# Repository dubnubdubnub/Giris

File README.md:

# Giris

An open source 32 key/half (64 total) **analog TMR split ortholinear keyboard** & 6 key macropad/dev board (`hw/TMR2615F_osu_pad`). 
Layout is similar to Keeb.io Iris with an extra column. Uses TMR2615F, 4:8 TMUX1574RSVR mux, & AT32F405. Link is UART over type-c cable.

There are 3 unique modes of operation: 
- standalone
- half A --> half B --> computer
- computer A <-- half A <--> half B --> computer B
    - Giris doubles as a KVM, you can control which computer you're typing on with a programmable macro
    - Relevant power circuitry to prevent backfeeding (GROUNDS ARE STILL BONDED!!!)

Done by Human:
- `hw/` — KiCad schematics and layout. `TMR2615F_osu_pad` is the 6-key development board the
  firmware is brought up on; `giris` is the full-size split.
- `mech/` — plates and frames.

Done by LLM + Human:
- `fw/` — firmware, written from scratch in C on the Artery BSP with TinyUSB. 8 kHz USB HS polling,
  8 kHz inter-half link. Host tools and a WebHID configurator live in `fw/tools/`.

## Schematics and photos

PDFs:

- **osu pad dev board** (built and running, pictured above):
  [schematic](hw/TMR2615F_osu_pad/output/TMR2615F_osu_pad.pdf) ·
  [PCB layers](hw/TMR2615F_osu_pad/output/TMR2615F_osu_pad-layers.pdf)
- **Giris split** (in layout): [schematic](hw/giris/output/giris.pdf)
- **More photos and video** of built boards: [`docs/photos/`](docs/photos/)

The schematic PDFs draw the per-key sheet once and list each key's designators at the end;
regenerate them with `hw/tools/sch_pdf.py`.

## Setup

This repo uses git submodules for its shared footprint/3D-model library (`hw/library`) and `hw/marbastlib`. **The 3D bodies will not appear in KiCad's 3D viewer unless the submodules are checked out**; `.step` files live in `hw/library/packages3d/`.

Clone with submodules:

```bash
git clone --recurse-submodules https://github.com/dubnubdubnub/Giris.git
```

If you already cloned without `--recurse-submodules`, initialize them after the fact:

```bash
git submodule update --init --recursive
```

> Note: `hw/marbastlib` may print an error while recursing into a nested `.history` submodule. That is harmless — it is upstream and holds no 3D models the boards need.

## 3D models

Footprint 3D bodies resolve from three locations:

- `${KICAD10_3DMODEL_DIR}/…` — the standard models shipped with KiCad.
- `${KIPRJMOD}/../library/packages3d/…` — this repo's `hw/library` submodule (must be checked out; see Setup).

When adding new 3D models to a board, reference them with one of the path variables above rather than a bare relative path (e.g. `../../packages3d/…`), so they resolve regardless of where the repo is cloned.

## Licence

Giris uses two licences:

| What | Licence | File |
|---|---|---|
| Firmware, host tools, web configurator, docs | **Apache-2.0** | [`LICENSE`](LICENSE) |
| Hardware — schematics, PCB, magnet models (`hw/`) | **CERN-OHL-P v2** | [`hw/LICENSE`](hw/LICENSE) |

Both are permissive: use it, change it, build it, sell it, no obligation to
publish your changes. Apache-2.0 additionally carries an explicit patent grant.
CERN-OHL-P is the hardware equivalent — software licences are written about
copying source, not about manufacturing a board.

New source files should carry an SPDX header:

```c
/* SPDX-License-Identifier: Apache-2.0
 * Copyright 2026 Isaac Chiu
 */
```

### Third-party code

[`THIRD_PARTY.md`](THIRD_PARTY.md) is the full inventory; [`NOTICE`](NOTICE)
carries the attributions that must accompany a distributed **binary**.

The short version: TinyUSB (MIT) and the ArteryTek BSP are fetched at build time
by `fw/tools/fetch-deps.sh` and are not in this repository, though both are linked
into firmware binaries. Three Artery-derived files *are* committed — the startup
file, the linker script and `at32f402_405_conf.h` — and keep Artery's notice
rather than Giris'. Note that Artery ships two licence statements that disagree;
`THIRD_PARTY.md` explains which one to rely on.

### Why the firmware is not GPL

Giris is written from scratch. libhmk, minipad, DeskHop and the VIA app are
GPL-3.0; QMK, vial-qmk and Keychron's fork are GPL-2.0. All were read as
references and **no source file was ever pasted out of any of them**. That is a
deliberate, ongoing constraint, not an accident — copying so much as a descriptor
struct would make this firmware copyleft.

This matters most for the USB XUSB (Xbox controller) interface, where both
reference implementations — libhmk and Keychron's QMK fork — are copyleft. Write
it from Microsoft's own specification instead:

> **[MS-XUSBI]** — *Xbox Universal Serial Bus Protocol (XUSB) Interface Extension*
> <https://learn.microsoft.com/en-us/openspecs/windows_protocols/ms-xusbi/c79474e7-3968-43d1-8d2f-175d47bef43e>

It gives the class triple and the 20-byte report normatively, and its Open
Specifications notice explicitly permits copying the documentation in order to
build implementations of it. [`THIRD_PARTY.md`](THIRD_PARTY.md) records the
limits of that permission — notably that no patent grant is established.

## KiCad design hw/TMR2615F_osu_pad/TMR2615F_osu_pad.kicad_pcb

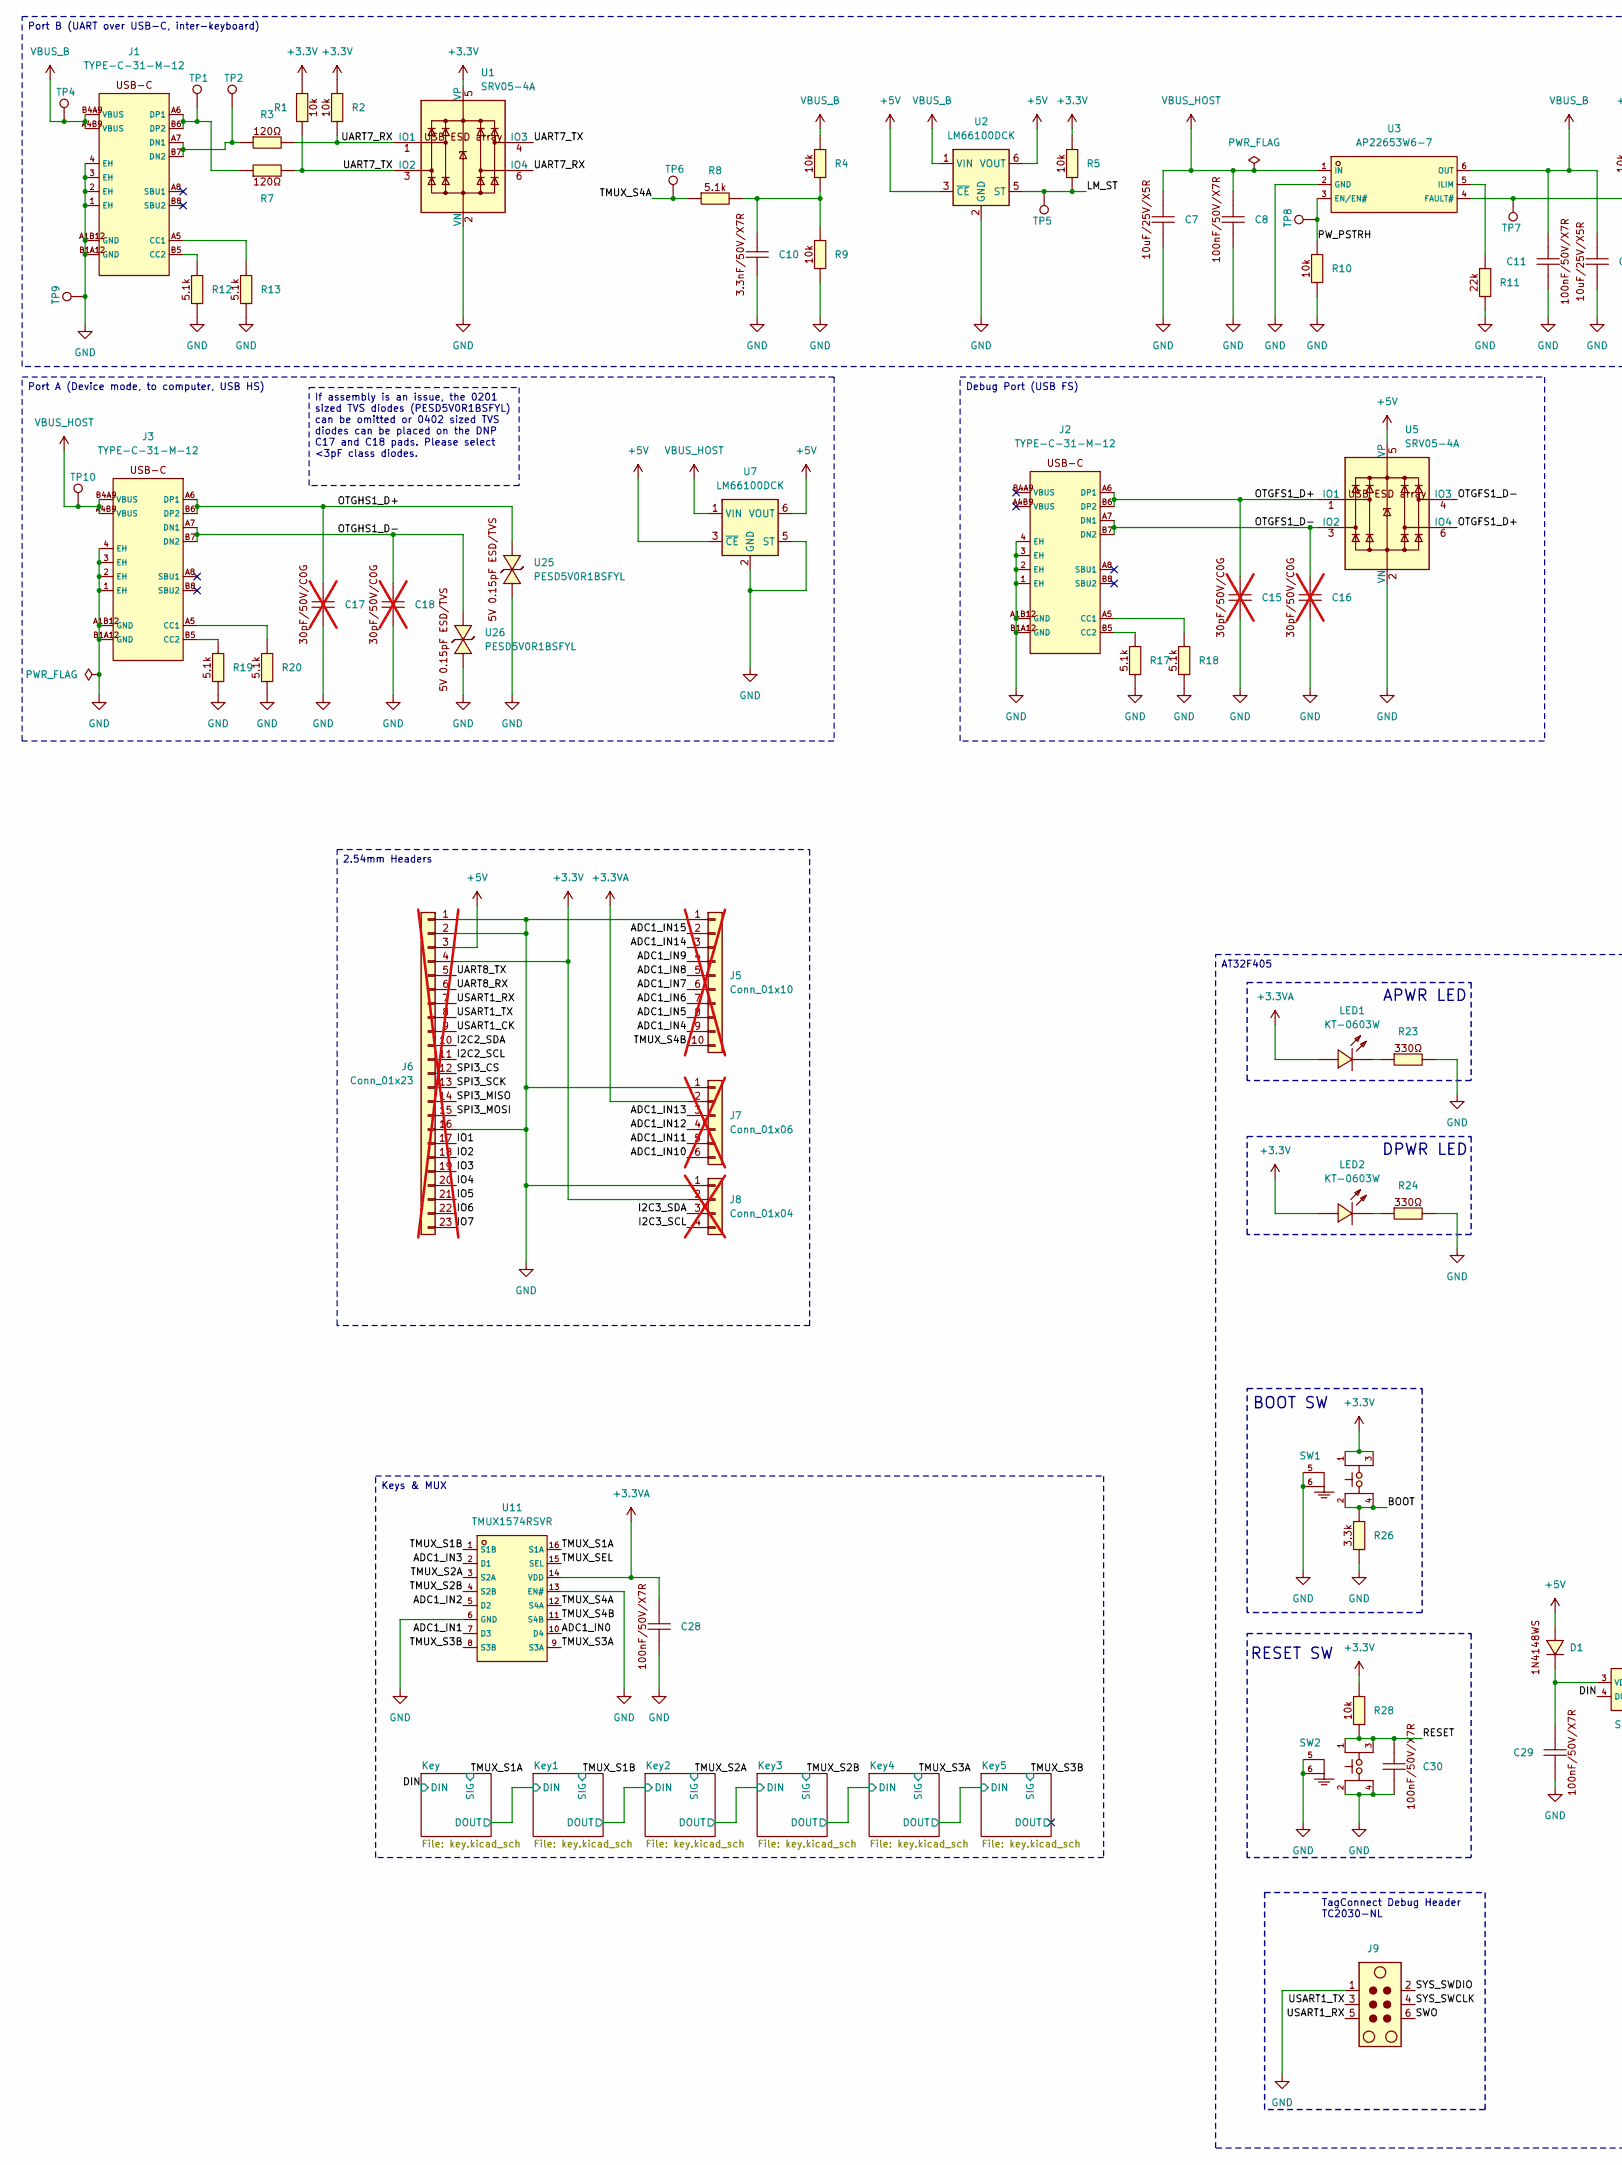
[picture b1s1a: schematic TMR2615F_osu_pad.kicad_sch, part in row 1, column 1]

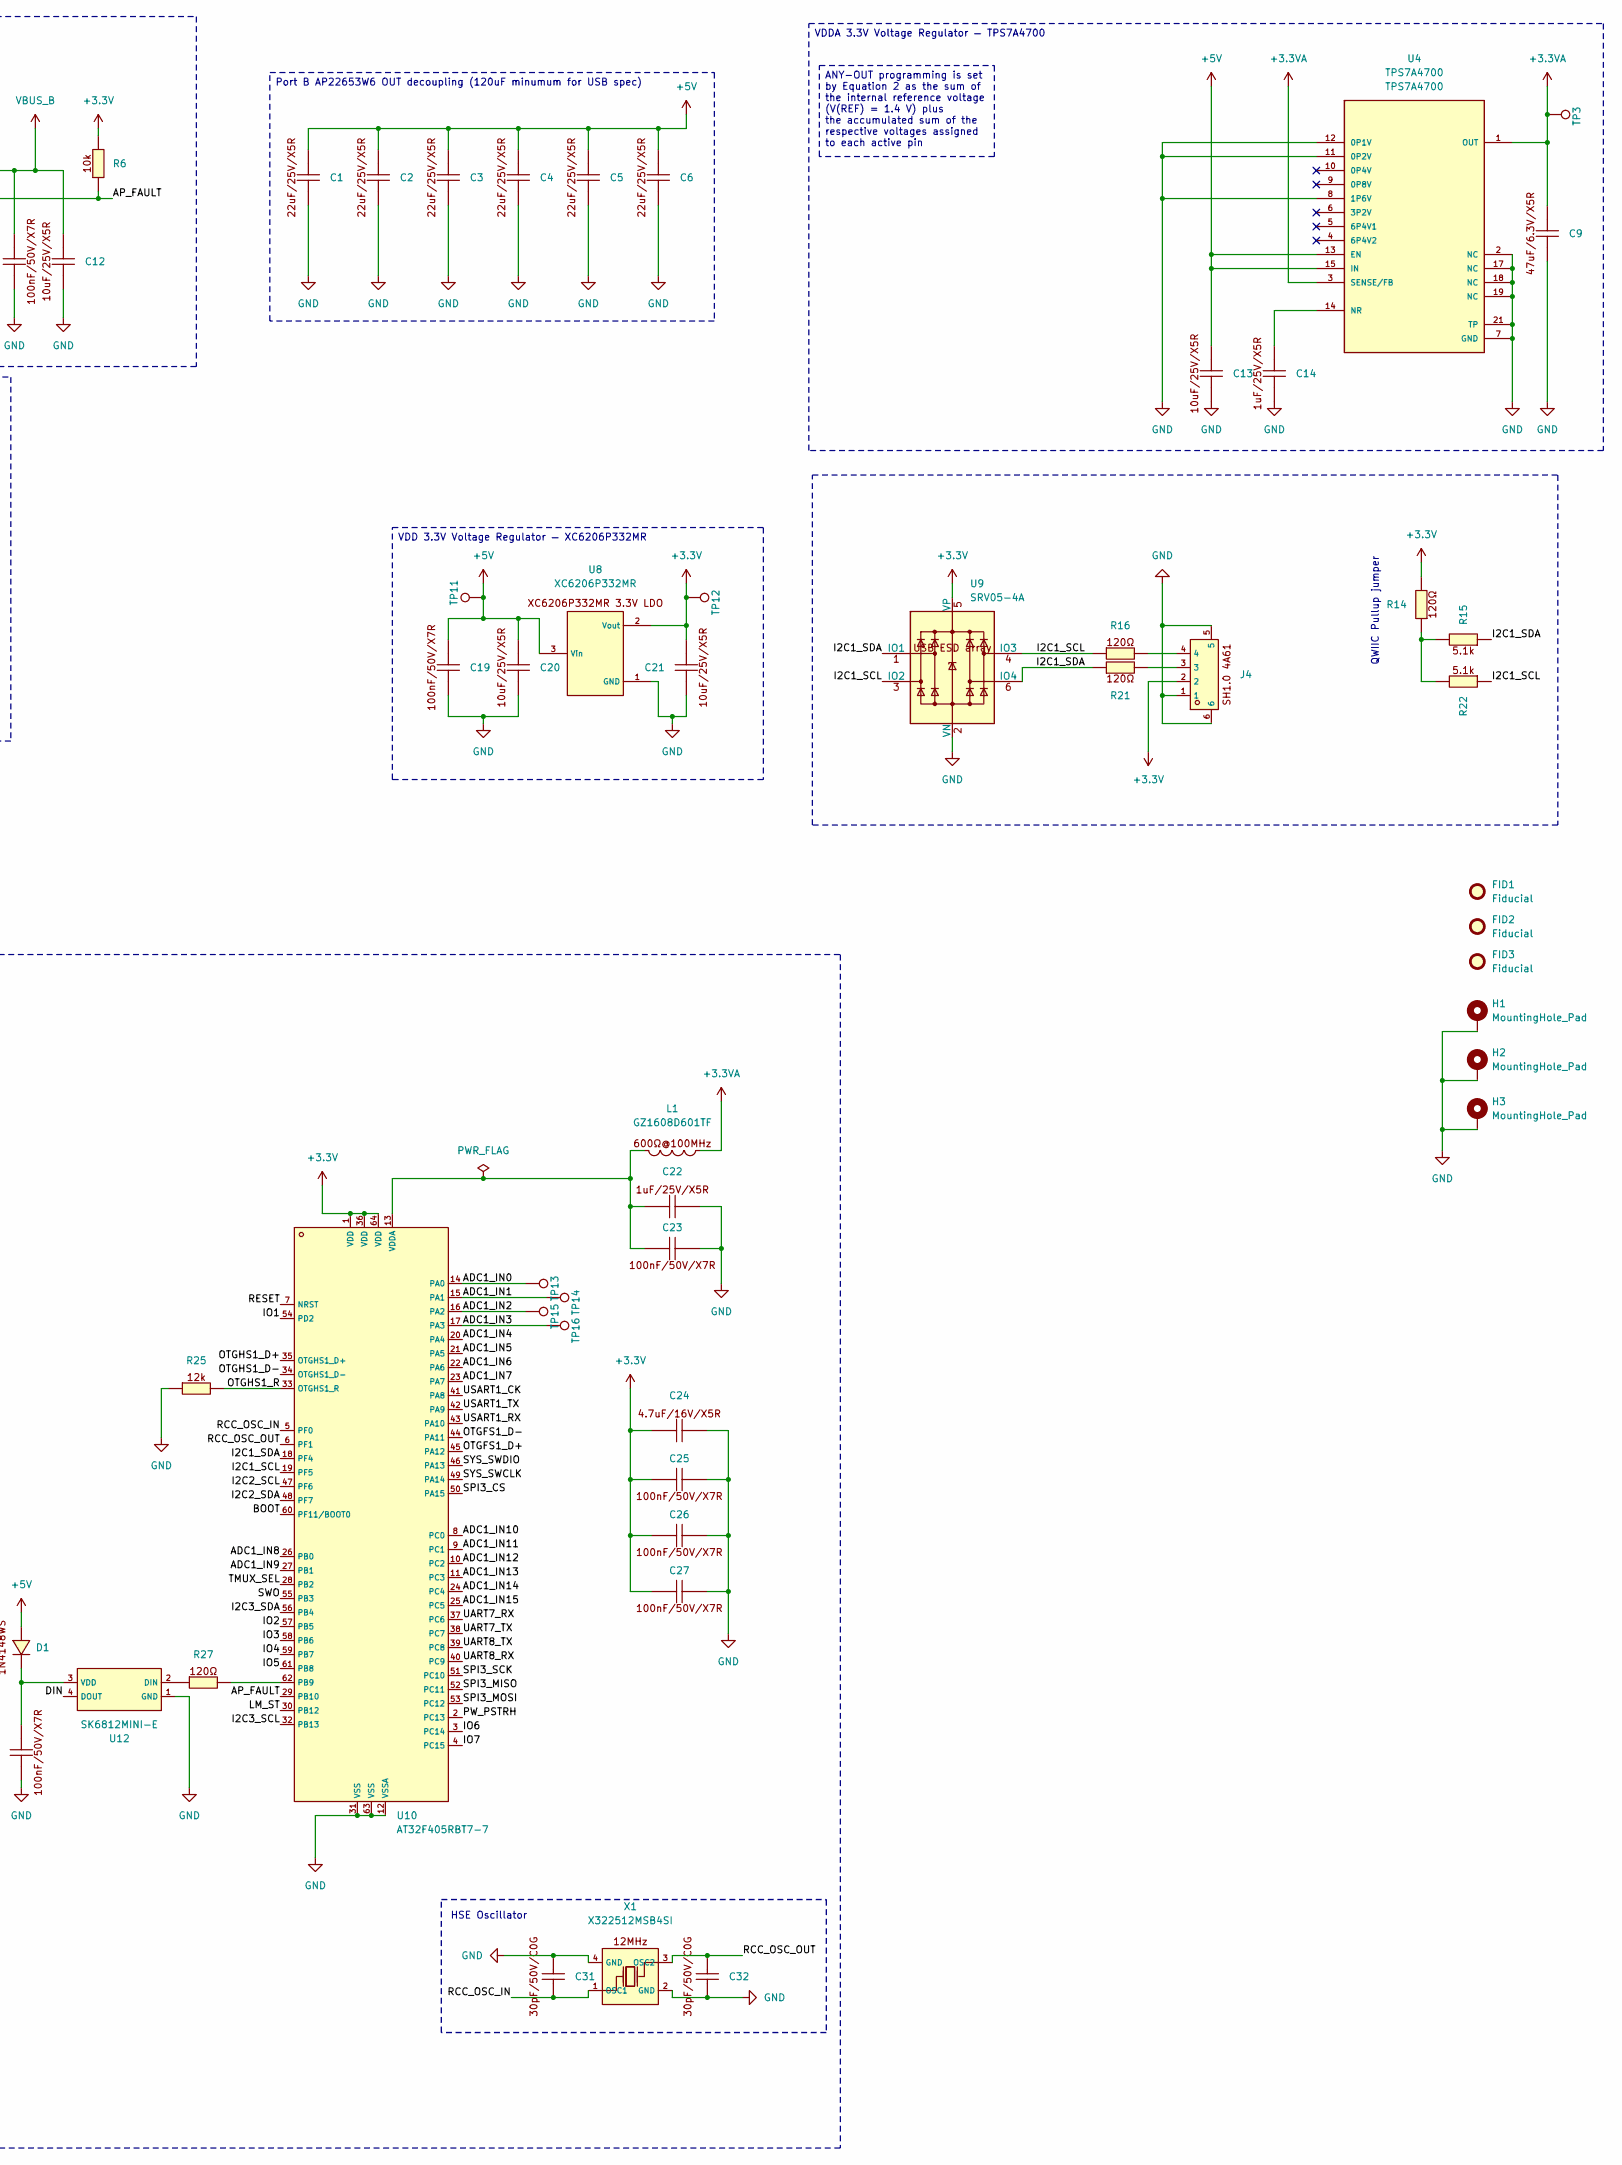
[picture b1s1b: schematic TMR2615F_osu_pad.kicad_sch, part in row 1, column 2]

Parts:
C1, C2, C3, C4, C5, C6: CL21A226MAQNNNE; C_0805_2012Metric; LCSC C45783
C7, C12, C13, C20, C21: CL21A106KAYNNNE; C_0805_2012Metric; LCSC C15850
C8, C11, C19, C23, C25, C26, C27, C28, C29, C30: CL05B104KB54PNC; C_0402_1005Metric; LCSC C307331
C9: CL21A476MQYNNNE; C_0805_2012Metric; LCSC C16780
C10: CL10B332KB8NNNC; C_0603_1608Metric; LCSC C1613
C14, C22: CL05A105KA5NQNC; C_0402_1005Metric; LCSC C52923
C15, C16, C17, C18: 0402CG300J500NT; C_0402_1005Metric; LCSC C1570; not fitted
C24: CL10A475KO8NNNC; C_0603_1608Metric; LCSC C19666
C31, C32: 0402CG300J500NT; C_0402_1005Metric; LCSC C1570
D1: 1N4148WS_T4; D_SOD-323_HandSoldering; LCSC C2128
FID1, FID2, FID3: Fiducial; Fiducial_1mm_Mask2mm
H1, H2, H3: MountingHole_Pad; MountingHole_2.2mm_M2_Pad_Via
J1, J2, J3: TYPE-C-31-M-12; USB-C_SMD-TYPE-C-31-M-12_1; LCSC C165948
J4: XY-SH1_0-4A61; CONN-SMD_4P-P1.00_XYECONN_XY-SH1.0-4A61; LCSC C19271998
J5: Conn_01x10; PinHeader_1x10_P2.54mm_Vertical; not fitted
J6: Conn_01x23; PinHeader_1x23_P2.54mm_Vertical; not fitted
J7: Conn_01x06; PinHeader_1x06_P2.54mm_Vertical; not fitted
J8: Conn_01x04; PinHeader_1x04_P2.54mm_Vertical; not fitted
J9: Tag-Connect_TC2030-IDC-NL_2x03_P1.27mm_Vertical
L1: GZ1608D601TF; L_0603_1608Metric; LCSC C1002
LED1, LED2: KT-0603W; LED0603-R-RD_WHITE; LCSC C2290
R1, R2, R4, R5, R6, R9, R10, R28: 0402WGF1002TCE; R_0402_1005Metric; LCSC C25744
R3, R7, R14, R16, R21, R27: 0402WGF1200TCE; R_0402_1005Metric; LCSC C25079
R8, R12, R13, R15, R17, R18, R19, R20, R22: 0402WGF5101TCE; R_0402_1005Metric; LCSC C25905
R11: 0402WGF2202TCE; R_0402_1005Metric; LCSC C25768
R23, R24: 0402WGF3300TCE; R_0402_1005Metric; LCSC C25104
R25: 0402WGF1202TCE; R_0402_1005Metric; LCSC C25752
R26: 0402WGF3301TCE; R_0402_1005Metric; LCSC C25890
SW1, SW2: SKSGPAE010; SW-SMD_SKSGAAE010; LCSC C125045
TP1, TP2, TP3, TP4, TP5, TP6, TP7, TP8, TP9, TP10, TP11, TP12, TP13, TP14, TP15, TP16: TestPoint; TestPoint_Pad_D1.0mm
U1, U5, U9: SRV05-4A; SOT-23-6; LCSC ID C20615829
U2, U7: LM66100DCK; SOT-363_SC-70-6; LCSC C2869734
U3: AP22653W6-7; SOT-23-6_L2.9-W1.6-P0.95-LS2.8-BR; LCSC C2158037
U4: TPS7A4700; VQFN-20_L5.0-W5.0-P0.65-TL-EP; LCSC C28286
U8: XC6206P332MR; SOT-23-3_L2.9-W1.6-P1.90-LS2.8-BR; LCSC C5446
U10: AT32F405RBT7-7; LQFP-64_L7.0-W7.0-P0.40-LS9.0-BL; LCSC C47115472
U11: TMUX1574RSVR; UQFN-16_L2.6-W1.8-P0.40-BL; LCSC C2673120
U12: SK6812MINI-E; LED-SMD_4P-L3.2-W2.8-LS5.9_SK6812MINI-E; LCSC C5149201
U25, U26: PESD5V0R1BSFYL; SOD-962_L0.6-W0.3-BI; LCSC C461221
X1: X322512MSB4SI; LCSC C9002

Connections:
+3.3V: C21.1, C24.1, C25.2, C26.2, C27.2, J4.2, J6.4, J8.2, LED2.1 (A), R1.2, R2.2, R5.2, R6.2, R14.2, R28.2, SW1.1, SW1.3, TP12.1 (1_1), U1.5 (VP), U8.2 (Vout), U9.5 (VP), U10.1 (VDD), U10.36 (VDD), U10.64 (VDD)
+3.3VA: C9.2, C28.2, J7.2, L1.2, LED1.1 (A), TP3.1 (1_1), U4.1 (OUT), U4.3 (SENSE/FB), U4.20 (OUT), U11.14 (VDD); also elsewhere on the board
+5V: C1.2, C2.2, C3.2, C4.2, C5.2, C6.2, C13.2, C19.2, C20.2, D1.2 (A), J6.3, TP11.1 (1_1), U2.3 (~CE), U2.6 (VOUT), U4.13 (EN), U4.15 (IN), U4.16 (IN), U5.5 (VP), U7.3 (~CE), U7.6 (VOUT), U8.3 (Vin); also elsewhere on the board
/ADC1_IN0: TP13.1 (1_1), U10.14 (PA0), U11.10 (D4)
/ADC1_IN1: TP14.1 (1_1), U10.15 (PA1), U11.7 (D3)
/ADC1_IN2: TP15.1 (1_1), U10.16 (PA2), U11.5 (D2)
/ADC1_IN3: TP16.1 (1_1), U10.17 (PA3), U11.2 (D1)
/ADC1_IN4: J5.9, U10.20 (PA4)
/ADC1_IN5: J5.8, U10.21 (PA5)
/ADC1_IN6: J5.7, U10.22 (PA6)
/ADC1_IN7: J5.6, U10.23 (PA7)
/ADC1_IN8: J5.5, U10.26 (PB0)
/ADC1_IN9: J5.4, U10.27 (PB1)
/ADC1_IN10: J7.6, U10.8 (PC0)
/ADC1_IN11: J7.5, U10.9 (PC1)
/ADC1_IN12: J7.4, U10.10 (PC2)
/ADC1_IN13: J7.3, U10.11 (PC3)
/ADC1_IN14: J5.3, U10.24 (PC4)
/ADC1_IN15: J5.2, U10.25 (PC5)
/AP_FAULT: R6.1, TP7.1 (1_1), U3.4 (FAULT#), U10.29 (PB10)
/BOOT: R26.2, SW1.2, SW1.4, U10.60 (PF11/BOOT0)
/DIN: U12.4 (DOUT); also elsewhere on the board
/I2C1_SCL: R16.1, R22.1, U9.3 (IO2), U9.4 (IO3), U10.19 (PF5)
/I2C1_SDA: R15.1, R21.1, U9.1 (IO1), U9.6 (IO4), U10.18 (PF4)
/I2C2_SCL: J6.11, U10.47 (PF6)
/I2C2_SDA: J6.10, U10.48 (PF7)
/I2C3_SCL: J8.4, U10.32 (PB13)
/I2C3_SDA: J8.3, U10.56 (PB4)
/IO1: J6.17, U10.54 (PD2)
/IO2: J6.18, U10.57 (PB5)
/IO3: J6.19, U10.58 (PB6)
/IO4: J6.20, U10.59 (PB7)
/IO5: J6.21, U10.61 (PB8)
/IO6: J6.22, U10.3 (PC14)
/IO7: J6.23, U10.4 (PC15)
/LM_ST: R5.1, TP5.1 (1_1), U2.5 (ST), U10.30 (PB12)
/OTGFS1_D+: C15.2, J2.A6 (DP1), J2.B6 (DP2), U5.1 (IO1), U5.6 (IO4), U10.45 (PA12)
/OTGFS1_D-: C16.2, J2.A7 (DN1), J2.B7 (DN2), U5.3 (IO2), U5.4 (IO3), U10.44 (PA11)
/OTGHS1_D+: C17.2, J3.A6 (DP1), J3.B6 (DP2), U10.35 (OTGHS1_D+), U25.2
/OTGHS1_D-: C18.2, J3.A7 (DN1), J3.B7 (DN2), U10.34 (OTGHS1_D-), U26.2
/OTGHS1_R: R25.2, U10.33 (OTGHS1_R)
/PW_PSTRH: R10.2, TP8.1 (1_1), U3.3 (EN/EN#), U10.2 (PC13)
/RCC_OSC_IN: C31.1, U10.5 (PF0), X1.1 (OSC1)
/RCC_OSC_OUT: C32.2, U10.6 (PF1), X1.3 (OSC2)
/RESET: C30.2, R28.1, SW2.1, SW2.3, U10.7 (NRST)
/SPI3_CS: J6.12, U10.50 (PA15)
/SPI3_MISO: J6.14, U10.52 (PC11)
/SPI3_MOSI: J6.15, U10.53 (PC12)
/SPI3_SCK: J6.13, U10.51 (PC10)
/SWO: J9.6, U10.55 (PB3)
/SYS_SWCLK: J9.4, U10.49 (PA14)
/SYS_SWDIO: J9.2, U10.46 (PA13)
/TMUX_S1A: U11.16 (S1A); also elsewhere on the board
/TMUX_S1B: U11.1 (S1B); also elsewhere on the board
/TMUX_S2A: U11.3 (S2A); also elsewhere on the board
/TMUX_S2B: U11.4 (S2B); also elsewhere on the board
/TMUX_S3A: U11.9 (S3A); also elsewhere on the board
/TMUX_S3B: U11.8 (S3B); also elsewhere on the board
/TMUX_S4A: R8.1, TP6.1 (1_1), U11.12 (S4A)
/TMUX_S4B: J5.10, U11.11 (S4B)
/TMUX_SEL: U10.28 (PB2), U11.15 (SEL)
/UART7_RX: R2.1, R3.2, U1.1 (IO1), U1.6 (IO4), U10.37 (PC6)
/UART7_TX: R1.1, R7.2, U1.3 (IO2), U1.4 (IO3), U10.38 (PC7)
/UART8_RX: J6.6, U10.40 (PC9)
/UART8_TX: J6.5, U10.39 (PC8)
/USART1_CK: J6.9, U10.41 (PA8)
/USART1_RX: J6.7, J9.5, U10.43 (PA10)
/USART1_TX: J6.8, J9.3, U10.42 (PA9)
GND: C1.1, C2.1, C3.1, C4.1, C5.1, C6.1, C7.2, C8.1, C9.1, C10.1, C11.1, C12.2, C13.1, C14.1, C15.1, C16.1, C17.1, C18.1, C19.1, C20.1, C21.2, C22.2, C23.1, C24.2, C25.1, C26.1, C27.1, C28.1, C29.1, C30.1, C31.2, C32.1, H1.1 (1_1), H2.1 (1_1), H3.1 (1_1), J1.1 (EH), J1.2 (EH), J1.3 (EH), J1.4 (EH), J1.A1B12 (GND), J1.B1A12 (GND), J2.1 (EH), J2.2 (EH), J2.3 (EH), J2.4 (EH), J2.A1B12 (GND), J2.B1A12 (GND), J3.1 (EH), J3.2 (EH), J3.3 (EH), J3.4 (EH), J3.A1B12 (GND), J3.B1A12 (GND), J4.1, J4.5, J4.6, J5.1, J6.1, J6.2, J6.16, J7.1, J8.1, J9.1, R9.1, R10.1, R11.1, R12.1, R13.1, R17.1, R18.1, R19.1, R20.1, R23.2, R24.2, R25.1, R26.1, SW1.5, SW1.6, SW2.2, SW2.4, SW2.5, SW2.6, TP9.1 (1_1), U1.2 (VN), U2.2 (GND), U3.2 (GND), U4.2 (NC), U4.7 (GND), U4.8 (1P6V), U4.11 (0P2V), U4.12 (0P1V), U4.17 (NC), U4.18 (NC), U4.19 (NC), U4.21 (TP), U5.2 (VN), U7.2 (GND), U7.5 (ST), U8.1 (GND), U9.2 (VN), U10.12 (VSSA), U10.31 (VSS), U10.63 (VSS), U11.6 (GND), U11.13 (EN#), U12.1 (GND), U25.1, U26.1, X1.2 (GND), X1.4 (GND); also elsewhere on the board
unnamed: C10.2, R4.1, R8.2, R9.2
unnamed: C29.2, D1.1 (K), U12.3 (VDD)
unnamed: J1.A5 (CC1), R13.2
unnamed: J1.B5 (CC2), R12.2
unnamed: J1.A7 (DN1), J1.B7 (DN2), R3.1, TP2.1 (1_1)
unnamed: J1.A6 (DP1), J1.B6 (DP2), R7.1, TP1.1 (1_1)
unnamed: J2.A5 (CC1), R18.2
unnamed: J2.B5 (CC2), R17.2
unnamed: J3.A5 (CC1), R20.2
unnamed: J3.B5 (CC2), R19.2
unnamed: J4.3, R21.2
unnamed: J4.4, R16.2
unnamed: LED1.2 (K), R23.1
unnamed: LED2.2 (K), R24.1
unnamed: R14.1, R15.2, R22.2
unnamed: R11.2, U3.5 (ILIM)
unnamed: C14.2, U4.14 (NR)
unnamed: R27.2, U10.62 (PB9)
unnamed: C22.1, C23.2, L1.1, U10.13 (VDDA)
unnamed: R27.1, U12.2 (DIN)
VBUS_B: C11.2, C12.1, J1.A4B9 (VBUS), J1.B4A9 (VBUS), R4.2, TP4.1 (1_1), U2.1 (VIN), U3.6 (OUT)
VBUS_HOST: C7.1, C8.2, J3.A4B9 (VBUS), J3.B4A9 (VBUS), TP10.1 (1_1), U3.1 (IN), U7.1 (VIN)

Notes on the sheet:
APWR LED
TagConnect Debug Header TC2030-NL
BOOT SW
QWIIC Pullup jumper
HSE Oscillator
RESET SW
DPWR LED
Keys & MUX
Port A (Device mode, to computer, USB HS)
AT32F405
Debug Port (USB FS)
If assembly is an issue, the 0201 sized TVS diodes (PESD5V0R1BSFYL) can be omitted or 0402 sized TVS diodes can be placed on the DNP C17 and C18 pads. Please select <3pF class diodes.
Port B (UART over USB-C, inter-keyboard)
Port B AP22653W6 OUT decoupling (120uF minumum for USB spec)
VDDA 3.3V Voltage Regulator — TPS7A4700
ANY-OUT programming is set by Equation 2 as the sum of the internal reference voltage (V(REF) = 1.4 V) plus the accumulated sum of the respective voltages assigned to each active pin
2.54mm Headers
VDD 3.3V Voltage Regulator — XC6206P332MR

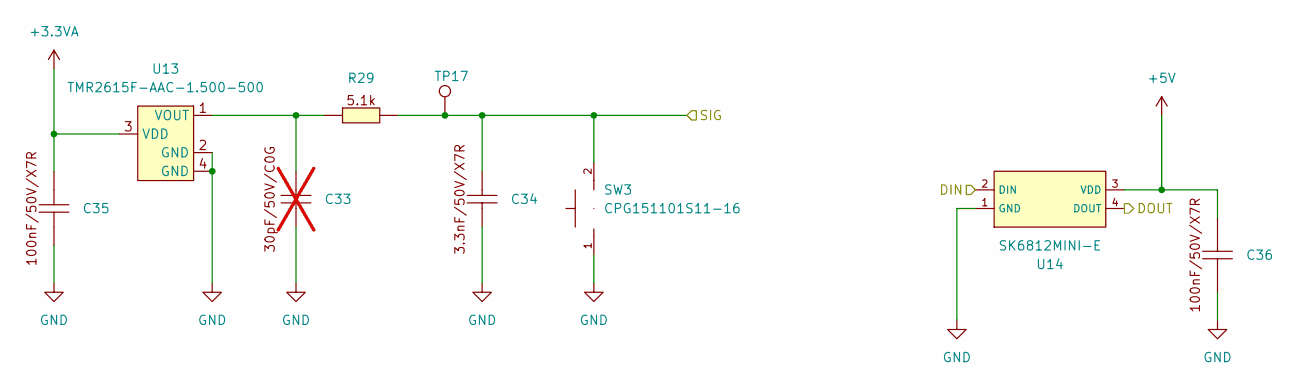
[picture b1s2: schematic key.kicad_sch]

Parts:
C33: 0402CG300J500NT; C_0402_1005Metric; LCSC C1570; not fitted
C34: CL10B332KB8NNNC; C_0603_1608Metric; LCSC C1613
C35, C36: CL05B104KB54PNC; C_0402_1005Metric; LCSC C307331
R29: 0402WGF5101TCE; R_0402_1005Metric; LCSC C25905
SW3: CPG151101S11-16; SMD_KEYBOARD-SW; LCSC C41430893
TP17: TestPoint; TestPoint_Pad_D1.0mm
U13: TMR2615F-AAC-1.500-500; DFN3L(1.6x1.6x0.5); MPN TMR2615F-AAC-1.500-500; LCSC C9900212297
U14: SK6812MINI-E; LED-SMD_4P-L3.2-W2.8-LS5.9_SK6812MINI-E; LCSC C5149201

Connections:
+3.3VA: C35.2, U13.3 (VDD); also elsewhere on the board
+5V: C36.2, U14.3 (VDD); also elsewhere on the board
/DIN: U14.2 (DIN); also elsewhere on the board
/Key/DOUT: U14.4 (DOUT); also elsewhere on the board
/TMUX_S1A: C34.2, R29.2, SW3.2, TP17.1 (1_1); also elsewhere on the board
GND: C33.1, C34.1, C35.1, C36.1, SW3.1, U13.2 (GND), U13.4 (GND), U14.1 (GND); also elsewhere on the board
unnamed: C33.2, R29.1, U13.1 (VOUT)

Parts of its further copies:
C37, C41, C45, C49, C53: 0402CG300J500NT; C_0402_1005Metric; LCSC C1570; not fitted
C38, C42, C46, C50, C54: CL10B332KB8NNNC; C_0603_1608Metric; LCSC C1613
C39, C40, C43, C44, C47, C48, C51, C52, C55, C56: CL05B104KB54PNC; C_0402_1005Metric; LCSC C307331
R30, R31, R32, R33, R34: 0402WGF5101TCE; R_0402_1005Metric; LCSC C25905
SW4, SW5, SW6, SW7, SW8: CPG151101S11-16; SMD_KEYBOARD-SW; LCSC C41430893
TP18, TP19, TP20, TP21, TP22: TestPoint; TestPoint_Pad_D1.0mm
U15, U17, U19, U21, U23: TMR2615F-AAC-1.500-500; DFN3L(1.6x1.6x0.5); MPN TMR2615F-AAC-1.500-500; LCSC C9900212297
U16, U18, U20, U22, U24: SK6812MINI-E; LED-SMD_4P-L3.2-W2.8-LS5.9_SK6812MINI-E; LCSC C5149201

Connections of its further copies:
+3.3VA: C39.2, C43.2, C47.2, C51.2, C55.2, U15.3 (VDD), U17.3 (VDD), U19.3 (VDD), U21.3 (VDD), U23.3 (VDD); also elsewhere on the board
+5V: C40.2, C44.2, C48.2, C52.2, C56.2, U16.3 (VDD), U18.3 (VDD), U20.3 (VDD), U22.3 (VDD), U24.3 (VDD); also elsewhere on the board
/Key1/DOUT: U16.4 (DOUT), U18.2 (DIN)
/Key2/DOUT: U18.4 (DOUT), U20.2 (DIN)
/Key3/DOUT: U20.4 (DOUT), U22.2 (DIN)
/Key4/DOUT: U22.4 (DOUT), U24.2 (DIN)
/Key5/DOUT: U24.4 (DOUT)
/Key/DOUT: U16.2 (DIN); also elsewhere on the board
/TMUX_S1B: C38.2, R30.2, SW4.2, TP18.1 (1_1); also elsewhere on the board
/TMUX_S2A: C42.2, R31.2, SW5.2, TP19.1 (1_1); also elsewhere on the board
/TMUX_S2B: C46.2, R32.2, SW6.2, TP20.1 (1_1); also elsewhere on the board
/TMUX_S3A: C50.2, R33.2, SW7.2, TP21.1 (1_1); also elsewhere on the board
/TMUX_S3B: C54.2, R34.2, SW8.2, TP22.1 (1_1); also elsewhere on the board
GND: C37.1, C38.1, C39.1, C40.1, C41.1, C42.1, C43.1, C44.1, C45.1, C46.1, C47.1, C48.1, C49.1, C50.1, C51.1, C52.1, C53.1, C54.1, C55.1, C56.1, SW4.1, SW5.1, SW6.1, SW7.1, SW8.1, U15.2 (GND), U15.4 (GND), U16.1 (GND), U17.2 (GND), U17.4 (GND), U18.1 (GND), U19.2 (GND), U19.4 (GND), U20.1 (GND), U21.2 (GND), U21.4 (GND), U22.1 (GND), U23.2 (GND), U23.4 (GND), U24.1 (GND); also elsewhere on the board
unnamed: C37.2, R30.1, U15.1 (VOUT)
unnamed: C41.2, R31.1, U17.1 (VOUT)
unnamed: C45.2, R32.1, U19.1 (VOUT)
unnamed: C49.2, R33.1, U21.1 (VOUT)
unnamed: C53.2, R34.1, U23.1 (VOUT)

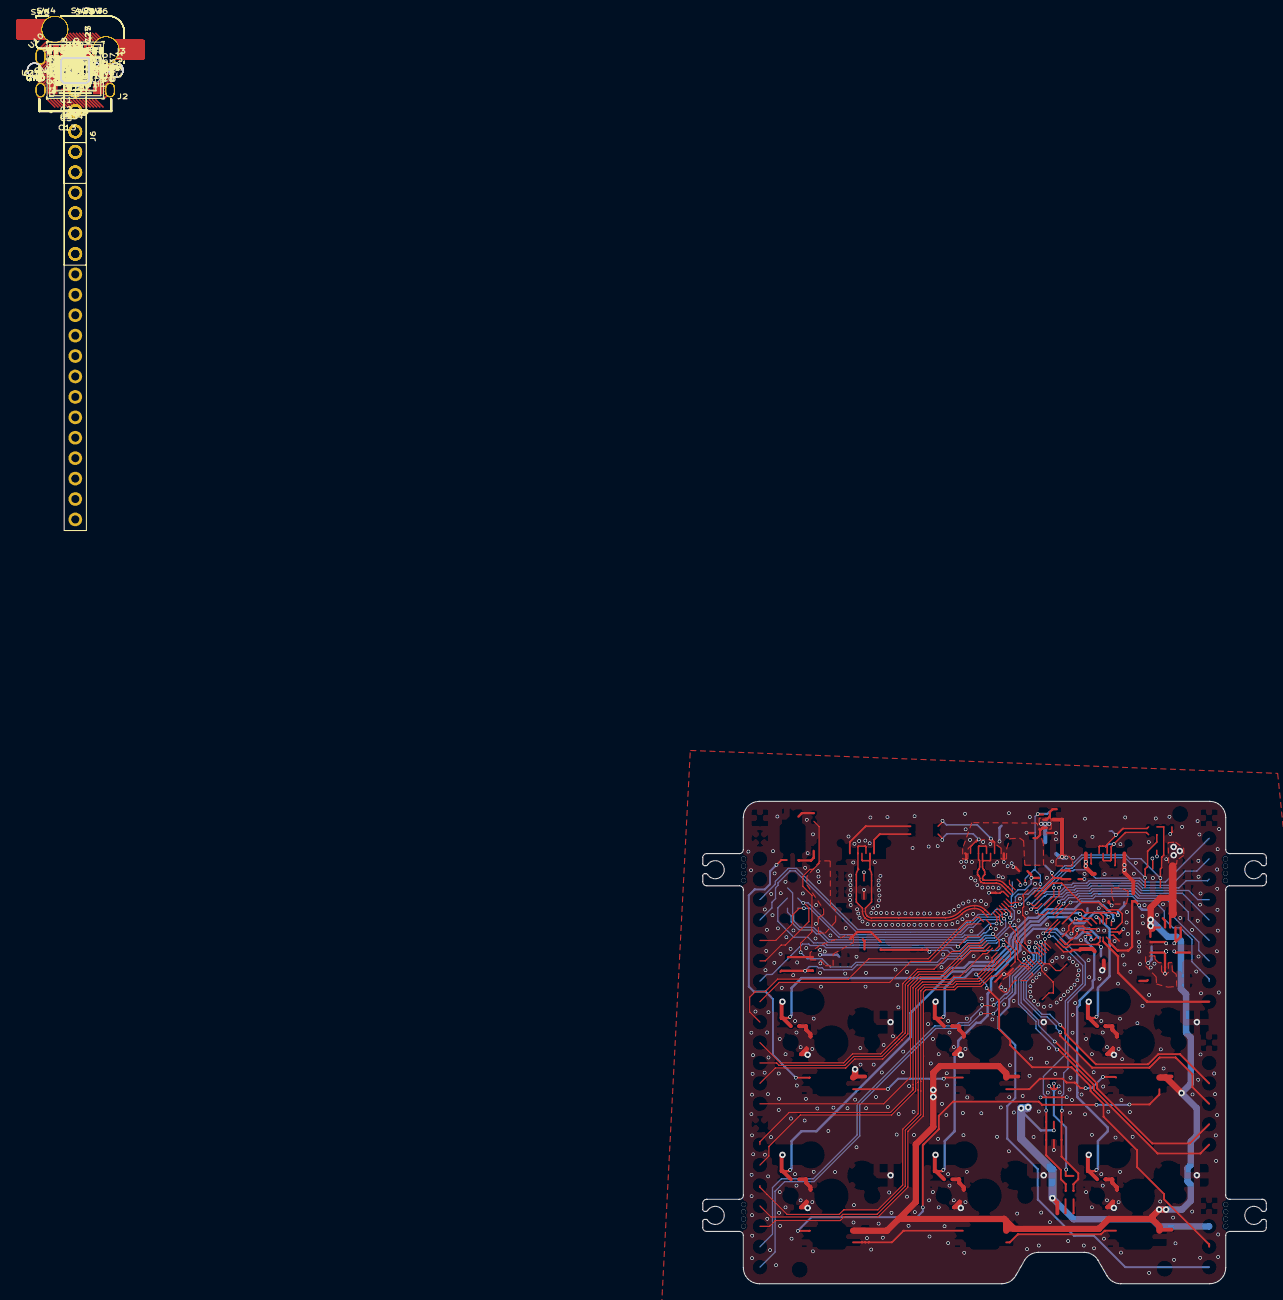
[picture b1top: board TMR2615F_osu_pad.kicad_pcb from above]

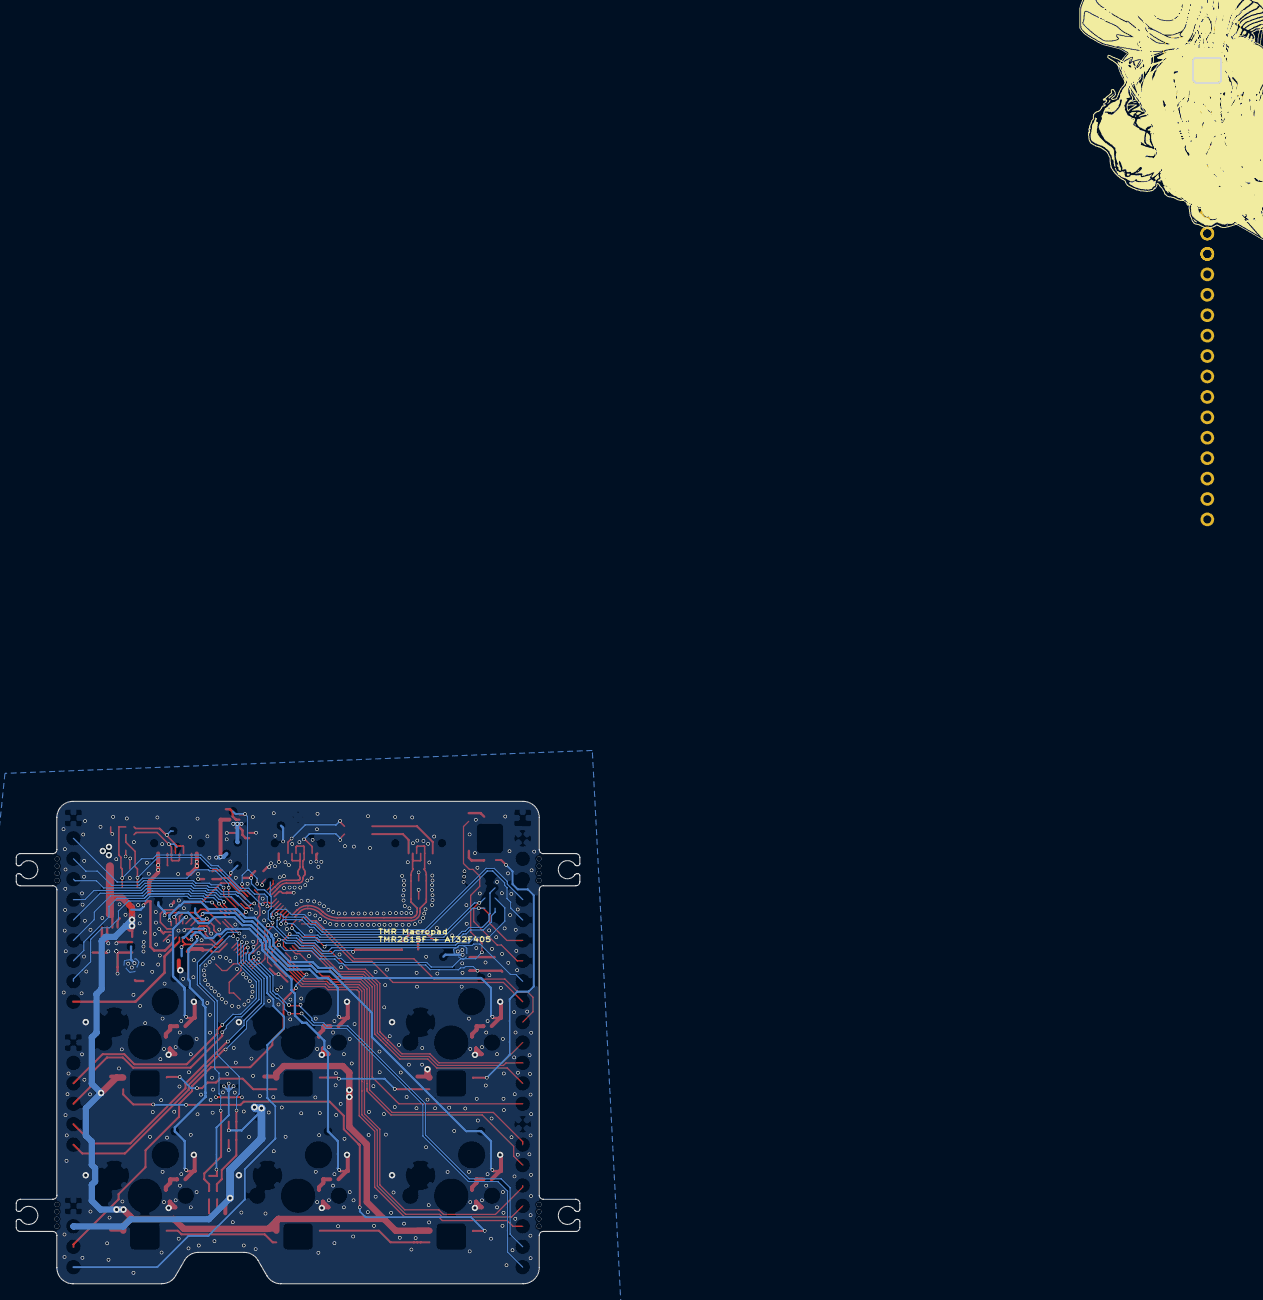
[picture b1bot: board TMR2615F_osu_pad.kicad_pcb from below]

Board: 4 copper layers, 3.5 x 3.1 mm, 165 parts (23 on the bottom side), 102 nets.

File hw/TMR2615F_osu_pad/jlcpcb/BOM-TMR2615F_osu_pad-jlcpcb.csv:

"Comment","Designator","Footprint","LCSC Part #"
"CL21A226MAQNNNE","C1,C2,C3,C4,C5,C6","C_0805_2012Metric","C45783"
"CL21A106KAYNNNE","C7,C12,C13,C20,C21","C_0805_2012Metric","C15850"
"CL05B104KB54PNC","C8,C11,C19,C23,C25,C26,C27,C28,C29,C30,C35,C36,C39,C40,C43,C44,C47,C48,C51,C52,C55,C56","C_0402_1005Metric","C307331"
"CL21A476MQYNNNE","C9","C_0805_2012Metric","C16780"
"CL10B473KB8NNNC","C10,C34,C38,C42,C46,C50,C54","C_0603_1608Metric","C1622"
"CL05A105KA5NQNC","C14,C22","C_0402_1005Metric","C52923"
"CL10A475KO8NNNC","C24","C_0603_1608Metric","C19666"
"0402CG300J500NT","C31,C32","C_0402_1005Metric","C1570"
"1N4148WS_T4","D1","D_SOD-323_HandSoldering","C2128"
"TYPE-C-31-M-12","J1,J2,J3","USB-C_SMD-TYPE-C-31-M-12_1","C165948"
"XY-SH1_0-4A61","J4","CONN-SMD_4P-P1.00_XYECONN_XY-SH1.0-4A61","C19271998"
"GZ1608D601TF","L1","L_0603_1608Metric","C1002"
"KT-0603W","LED1,LED2","LED0603-R-RD_WHITE","C2290"
"0402WGF1002TCE","R1,R2,R4,R5,R6,R9,R10,R26,R28","R_0402_1005Metric","C25744"
"0402WGF1200TCE","R3,R7,R14,R16,R21,R27","R_0402_1005Metric","C25079"
"0402WGF3300TCE","R8,R23,R24,R29,R30,R31,R32,R33,R34","R_0402_1005Metric","C25104"
"0402WGF2202TCE","R11","R_0402_1005Metric","C25768"
"0402WGF5101TCE","R12,R13,R15,R17,R18,R19,R20,R22","R_0402_1005Metric","C25905"
"0402WGF1202TCE","R25","R_0402_1005Metric","C25752"
"SKSGPAE010","SW1,SW2","SW-SMD_SKSGAAE010","C125045"
"CPG151101S11-16","SW3,SW4,SW5,SW6,SW7,SW8","SMD_KEYBOARD-SW","C41430893"
"TestPoint","TP1,TP2,TP3,TP4,TP5,TP6,TP7,TP8,TP9,TP10,TP11,TP12,TP13,TP14,TP15,TP16,TP17,TP18,TP19,TP20,TP21,TP22","TestPoint_Pad_D1.0mm",""
"SRV05-4A","U1,U5,U6,U9","SOT-23-6","C20615829"
"LM66100DCK","U2,U7","SOT-363_SC-70-6",""
"AP22653W6-7","U3","SOT-23-6_L2.9-W1.6-P0.95-LS2.8-BR","C2158037"
"TPS7A4700","U4","VQFN-20_L5.0-W5.0-P0.65-TL-EP",""
"XC6206P332MR","U8","SOT-23-3_L2.9-W1.6-P1.90-LS2.8-BR","C5446"
"AT32F405RBT7-7","U10","LQFP-64_L7.0-W7.0-P0.40-LS9.0-BL","C47115472"
"TMUX1574RSVR","U11","UQFN-16_L2.6-W1.8-P0.40-BL","C2673120"
"SK6812MINI-E","U12,U14,U16,U18,U20,U22,U24","LED-SMD_4P-L3.2-W2.8-LS5.9_SK6812MINI-E","C5149201"
"TMR2615F-AAC-1.500-500","U13,U15,U17,U19,U21,U23","DFN3L(1.6x1.6x0.5)","C9900212297"
"X322512MSB4SI","X1","X322512MSB4SI","C9002"

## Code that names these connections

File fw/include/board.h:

/* SPDX-License-Identifier: Apache-2.0
 * Copyright 2026 Isaac Chiu
 */
/*
 * board.h — Giris TMR2615F_osu_pad (6-key analog dev pad) pin map.
 *
 * Every assignment here was read out of the exported netlist, not the schematic
 * source:  kicad-cli sch export netlist --format kicadsexpr
 * See ../../hw/TMR2615F_osu_pad/firmware_architecture.md §11b.
 */
#ifndef GIRIS_BOARD_H
#define GIRIS_BOARD_H

#include "at32f402_405.h"

/* ---------------------------------------------------------------- clocks */
#define BOARD_HEXT_HZ        12000000U   /* mandatory: the OTG_HS PHY's only legal reference */
#define BOARD_SCLK_HZ       216000000U

/* ------------------------------------------------------------- analog in */
/* TMUX1574 (U11) 4x SPDT.  SEL low  -> A set: sensors U13/U17/U21 + VBUS_B sense
 *                          SEL high -> B set: sensors U15/U19/U23                */
#define MUX_SEL_PORT         GPIOB
#define MUX_SEL_PIN          GPIO_PINS_2      /* PB2 */

/* Mux outputs D1..D4 land on ADC1_IN3..IN0 (note the reversed order). */
#define ADC_CH_D1            3                /* PA3 — S1A/S1B */
#define ADC_CH_D2            2                /* PA2 — S2A/S2B */
#define ADC_CH_D3            1                /* PA1 — S3A/S3B */
#define ADC_CH_D4            0                /* PA0 — S4A = VBUS_B/2, S4B = J5.10 */

/* Six TMR2615F-AAC-1.500-500 sensors, all on the +3.3VA rail (TPS7A4700, U4).
 * 1.500 mV/V/Gs, offset 500 mV/V, +-500 Gs magnetic, electrical rails at +-300 Gs.
 * => 6.144 ADC counts per Gauss, and the ratiometric output tracks VDDA exactly.
 * NOTE: the F variant's output is INVERTED — counts fall as the key travels.     */
#define SENSOR_COUNT         6

/* Per-key chain as built: VOUT -> 30 pF -> 5.1 k -> 3.3 nF -> mux.
 * Respin target is 2.2 k + 47 nF (+ 100 R in each hotswap socket branch).        */

/* Kailh hotswap sockets SW3..SW8 sit on the SAME analog node with their other
 * side on GND, so a *mechanical* switch shorts the sensor node. A reading pinned
 * near the bottom rail means "mechanical key closed", not a fault.               */

/* ------------------------------------------------------------------ leds */
/* 7-pixel SK6812MINI-E chain. Pixel 0 (U12) is the sacrificial level-shifter on
 * the 1N4148-dropped ~4.3 V rail; pixels 1..6 are the per-key LEDs on +5 V.      */
#define LED_DATA_PORT        GPIOB
#define LED_DATA_PIN         GPIO_PINS_9      /* PB9 -> R27 120R -> U12.DIN */
#define LED_COUNT            7
#define LED_FIRST_KEY_PIXEL  1

/* ------------------------------------------------------------------ link */
/* Inter-board USB-C J1 carries a UART, not USB.
 *   J1 D+ (A6/B6) -> R7 120R -> PC7   (net /UART7_TX)
 *   J1 D- (A7/B7) -> R3 120R -> PC6   (net /UART7_RX)
 * Both have 10k pull-ups (R1/R2) and SRV05-4A (U1) clamps.
 *
 * CAREFUL: the net names are inverted relative to the silicon. PC6 is natively
 * USART6_TX/UART7_TX and PC7 is natively USART6_RX/UART7_RX, so this board's
 * "default" half is the one that must set CTRL2.TRPSWAP.
 *
 * Prefer USART6 (MUX8) over UART7 (MUX9): same pins, but APB2-clocked at 216 MHz,
 * giving an exact integer ladder of 13.5 / 12 / 9 / 8 / 6 Mbaud instead of a
 * 6.75 Mbaud ceiling.  Target 9 Mbaud.                                           */
#define LINK_PORT            GPIOC
#define LINK_PIN_PC6         GPIO_PINS_6
#define LINK_PIN_PC7         GPIO_PINS_7
#define LINK_DISCOVERY_BAUD  115200U    /* open-drain phase; ~500 kbaud is the ceiling */
#define LINK_RUN_BAUD        9000000U   /* push-pull phase on USART6 */

/* ----------------------------------------------------------------- power */
/* PC13 drives the AP22653 (U3) enable, ACTIVE HIGH, and sources 5 V out J1.
 * It is Hi-Z at reset and R27's 10k pulldown holds the switch OFF.
 *
 * DO NOT DRIVE THIS PIN until link arbitration has completed and the VBUS_B
 * divider (mux S4A -> ADC1_IN0) reads cold. If a peer answers the hail, that is
 * dual-host mode and NOBODY sources VBUS.                                        */
#define PWR_SOURCE_EN_PORT   GPIOC
#define PWR_SOURCE_EN_PIN    GPIO_PINS_13     /* PC13, net /PW_PSTRH */

#define LINK_POWERED_PORT    GPIOB
#define LINK_POWERED_PIN     GPIO_PINS_12     /* PB12, net /LM_ST — high = we are the slave */

#define PWR_FAULT_PORT       GPIOB
#define PWR_FAULT_PIN        GPIO_PINS_10     /* PB10, net /AP_FAULT — AP22653 overcurrent */

#define PWR_DEBOUNCE_MS      10               /* AP22653 FAULT# has a 6 ms deglitch */

/* PB12 is also OTGHS_ID in AF 0xA and PB13 is OTGHS_VBUS — never mux PB12 to
 * AF 0xA. This design is device-only; force device mode.                         */

/* ------------------------------------------------------------------- usb */
/* J3 = USB HS host port (dedicated OTGHS1_D+/D-/R pins; OTGHS1_R needs its
 *      external 12k 1% to ground).  This is the 8 kHz path.
 * J2 = USB FS, DATA ONLY — PA11/PA12, no VBUS net at all. This is the only port
 *      that can reach the factory ROM DFU (2e3c:df11).                           */

/* ------------------------------------------------------------ debug / io */
#define SCOPE_PORT           GPIOD
#define SCOPE_PIN            GPIO_PINS_2      /* PD2, net /IO1, on J6 pin 17 */

/* J9 = SWD: PA13 SWDIO, PA14 SWCLK, PB3 SWO, plus USART1 on PA9/PA10.
 * SW1 = BOOT0 (PF11), SW2 = NRST.                                                */

#endif /* GIRIS_BOARD_H */

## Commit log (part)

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2026-05-08 add osu_pad library tables, submodule pointer, and reference datasheets
    - Bump library submodule to e4c36d7 (adds AT32F405, TMUX1574, TPS7A4700,
    TMR2615x, hotswap, ferrite, RGB LED, and 33Ω resistor parts)
    - New sym-lib-table and fp-lib-table for osu_pad project
    - /refs: datasheets and Artery hardware-design guidance for the
    giris analog Hall-effect keyboard build
2026-05-26 relocate library/marbastlib submodules to hw/ root, re-import lost parts
    KiCad 10's File→Local History "Restore" recursively removes subdirs
    not in its snapshot. Moving the submodule working trees from inside
    hw/TMR2615F_osu_pad/ up to hw/ keeps them out of reach: KiCad can only
    nuke things inside the project folder, not siblings of it.
    - hw/TMR2615F_osu_pad/library → hw/library (URI re-pointed in lib-tables)
    - hw/marbastlib re-added (KiCad restore wiped it in last session)
2026-05-26 drop phantom Ideal_Diode__C lib-table entries
    Nothing in the schematic references Ideal_Diode__C — neither
    TMR2615F_osu_pad.kicad_sch nor key.kicad_sch contains any
    'Ideal_Diode__C:*' lib_id. The library submodule has never had
    Ideal_Diode__C.kicad_symdir or .pretty dirs either. The entries
    were leftovers; KiCad logs "library not found" on every load.
2026-05-27 bump library submodule: SK6812MINI-E footprint refresh
2026-05-27 bump library submodule to 7a4a7dd
    Library standardized on ${KIPRJMOD}/../library/ path convention and now
    ships TMR2615F.step + reference from DFN3L(1.6x1.6x0.5).
2026-05-27 add Connector_Pogo__C across hw/, scaffold giris project lib-tables
    - bump hw/library submodule for new Connector_Pogo__C (YTC1P-8535-01 / C5221289)
    - register Connector_Pogo__C in TMR2615F_osu_pad lib-tables
    - scaffold hw/giris/{sym,fp}-lib-table from TMR2615F's so the giris
    KiCad project can resolve all shared library categories via
    ${KIPRJMOD}/../library and ${KIPRJMOD}/../marbastlib
    - track hw/giris/giris.kicad_{pcb,pro,sch} project stubs and
2026-05-27 drop LDO__C from project lib-tables after library merge
    Library submodule collapsed LDO__C into Regulator_Linear__C. Bumps
    hw/library pointer and removes the now-dangling LDO__C entries from
    both projects' sym/fp lib-tables.
    Project source files (TMR2615F_osu_pad.kicad_{sch,pcb}) had their
    LDO__C: refs rewritten to Regulator_Linear__C: in the working tree;
    those files remain untracked so the rewrite will land whenever the
